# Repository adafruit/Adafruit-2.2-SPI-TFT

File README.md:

# Adafruit 2.2" 18-bit color TFT LCD display with microSD card breakout 

<a href="http://www.adafruit.com/products/1480"><br/>Click here to purchase one from the Adafruit shop</a>

These are the Eagle CAD files for the Adafruit 2.2" 18-bit color TFT LCD display with microSD card breakout:
  * https://www.adafruit.com/products/797 (older 220x178 HX8340BN version)
  * http://www.adafruit.com/products/1480 (newer 320x240 ILI9340 version)

This lovely little display breakout is the best way to add a small, colorful and bright display to any project. Since the display uses 3-wire SPI to communicate and has its own pixel-addressable frame buffer, it can be used with every kind of microcontroller. Even a very small one with low memory and few pins available! 

The 2.2" display has 220x176 color pixels. Unlike the low cost "Nokia 6110" and similar LCD displays, which are CSTN type and thus have poor color and slow refresh, this display is a true TFT! The TFT driver (HX8340) can display full 18-bit color (262,144 shades!). And the LCD will always come with the same driver chip so there's no worries that your code will not work from one to the other. 

The breakout has the TFT display soldered on (it uses a delicate flex-circuit connector) as well as a ultra-low-dropout 3.3V regulator and a 3/5V level shifter so you can use it with 3.3V or 5V power and logic. We also had a little space so we placed a microSD card holder so you can easily load full color bitmaps from a FAT16/FAT32 formatted microSD card.

## License

Adafruit invests time and resources providing this open source design, 
please support Adafruit and open-source hardware by purchasing 
products from Adafruit!

Designed by Limor Fried/Ladyada for Adafruit Industries.
Creative Commons Attribution/Share-Alike, all text above must be included in any redistribution
All text above must be included in any redistribution

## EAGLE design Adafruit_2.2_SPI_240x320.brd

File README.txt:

Adafruit 2.2" 18-bit color TFT LCD display with microSD card breakout

These are the Eagle CAD files for the Adafruit 2.2" 18-bit color TFT LCD display with microSD card breakout:
  ----> https://www.adafruit.com/products/797 (older 220x178 HX8340BN version)
  ----> http://www.adafruit.com/products/1480 (newer 320x240 ILI9340 version)

Adafruit invests time and resources providing this open source design, please support Adafruit and open-source hardware by purchasing products from Adafruit!

This lovely little display breakout is the best way to add a small, colorful and bright display to any project. Since the display uses 3-wire SPI to communicate and has its own pixel-addressable frame buffer, it can be used with every kind of microcontroller. Even a very small one with low memory and few pins available! 

The 2.2" display has 220x176 color pixels. Unlike the low cost "Nokia 6110" and similar LCD displays, which are CSTN type and thus have poor color and slow refresh, this display is a true TFT! The TFT driver (HX8340) can display full 18-bit color (262,144 shades!). And the LCD will always come with the same driver chip so there's no worries that your code will not work from one to the other. 

The breakout has the TFT display soldered on (it uses a delicate flex-circuit connector) as well as a ultra-low-dropout 3.3V regulator and a 3/5V level shifter so you can use it with 3.3V or 5V power and logic. We also had a little space so we placed a microSD card holder so you can easily load full color bitmaps from a FAT16/FAT32 formatted microSD card.

All text above must be included in any redistribution

Designed by Limor Fried/Ladyada for Adafruit Industries.
Creative Commons Attribution/Share-Alike, all text above must be included in any redistribution

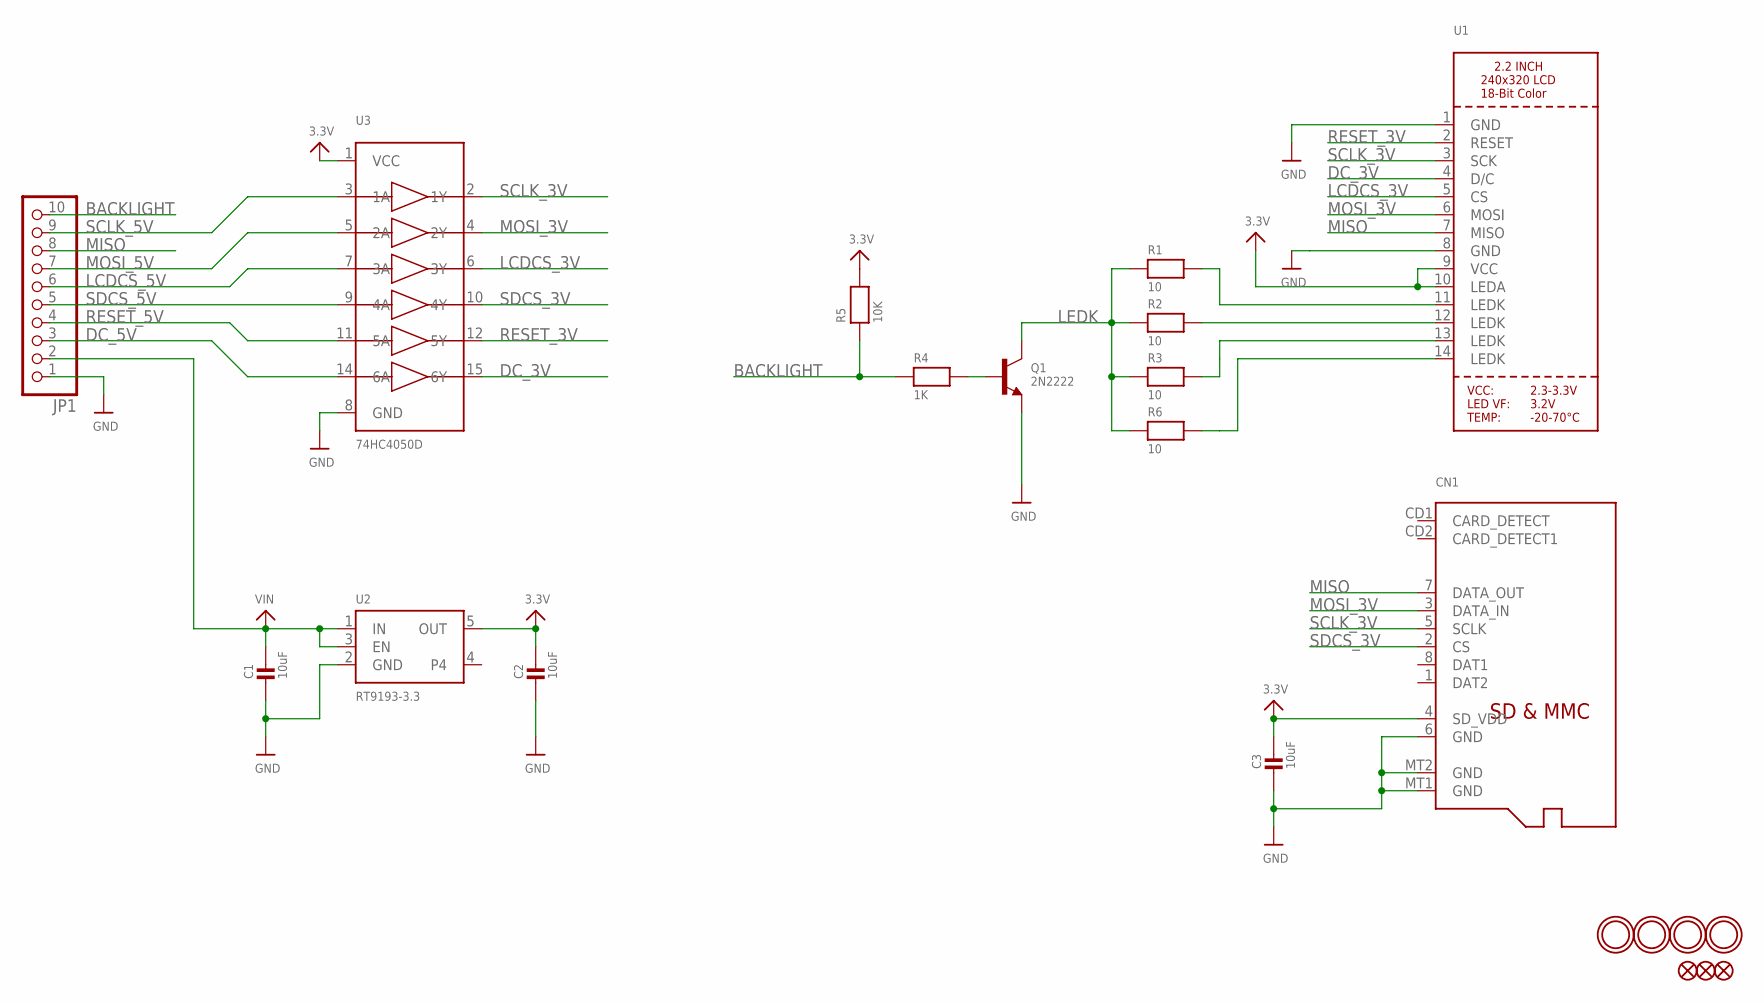
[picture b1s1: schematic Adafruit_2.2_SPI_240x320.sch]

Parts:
C1, C2, C3: 10uF; _0805MP
CN1: MICROSD
FID1, FID2, FID3: FIDUCIAL""; FIDUCIAL_1MM
JP1: HEADER-1X1070MIL; 1X10_ROUND70
Q1: 2N2222; SOT23-WIDE
R1, R2, R3, R6: 10; _0805MP
R4: 1K; _0805MP
R5: 10K; _0805MP
U1: DISP_LCD_TM022HDH26; TM022HDH26_2.2IN_LCD
U2: RT9193-3.3; SOT23-5
U3: 74HC4050D; SOIC16
U$2, U$3, U$4, U$5: MOUNTINGHOLE2.5; MOUNTINGHOLE_2.5_PLATED

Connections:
3.3V: C2.1, C3.1, CN1.4 (SD_VDD), R5.2, U1.9 (VCC), U1.10 (LEDA), U2.5 (OUT), U3.1 (VCC)
BACKLIGHT: JP1.10, R4.1, R5.1
DC_3V: U1.4 (D/C), U3.15 (6Y)
DC_5V: JP1.3, U3.14 (6A)
GND: C1.2, C2.2, C3.2, CN1.6 (GND), CN1.MT1 (GND), CN1.MT2 (GND), JP1.1, Q1.2 (E), U1.1 (GND), U1.8 (GND), U2.2 (GND), U3.8 (GND)
LCDCS_3V: U1.5 (CS), U3.6 (3Y)
LCDCS_5V: JP1.6, U3.7 (3A)
LEDK: Q1.3 (C), R1.1, R2.1, R3.1, R6.1
MISO: CN1.7 (DATA_OUT), JP1.8, U1.7 (MISO)
MOSI_3V: CN1.3 (DATA_IN), U1.6 (MOSI), U3.4 (2Y)
MOSI_5V: JP1.7, U3.5 (2A)
unnamed: R1.2, U1.11 (LEDK)
unnamed: R2.2, U1.12 (LEDK)
unnamed: R3.2, U1.13 (LEDK)
unnamed: Q1.1 (B), R4.2
unnamed: R6.2, U1.14 (LEDK)
RESET_3V: U1.2 (RESET), U3.12 (5Y)
RESET_5V: JP1.4, U3.11 (5A)
SCLK_3V: CN1.5 (SCLK), U1.3 (SCK), U3.2 (1Y)
SCLK_5V: JP1.9, U3.3 (1A)
SDCS_3V: CN1.2 (CS), U3.10 (4Y)
SDCS_5V: JP1.5, U3.9 (4A)
VIN: C1.1, JP1.2, U2.1 (IN), U2.3 (EN)

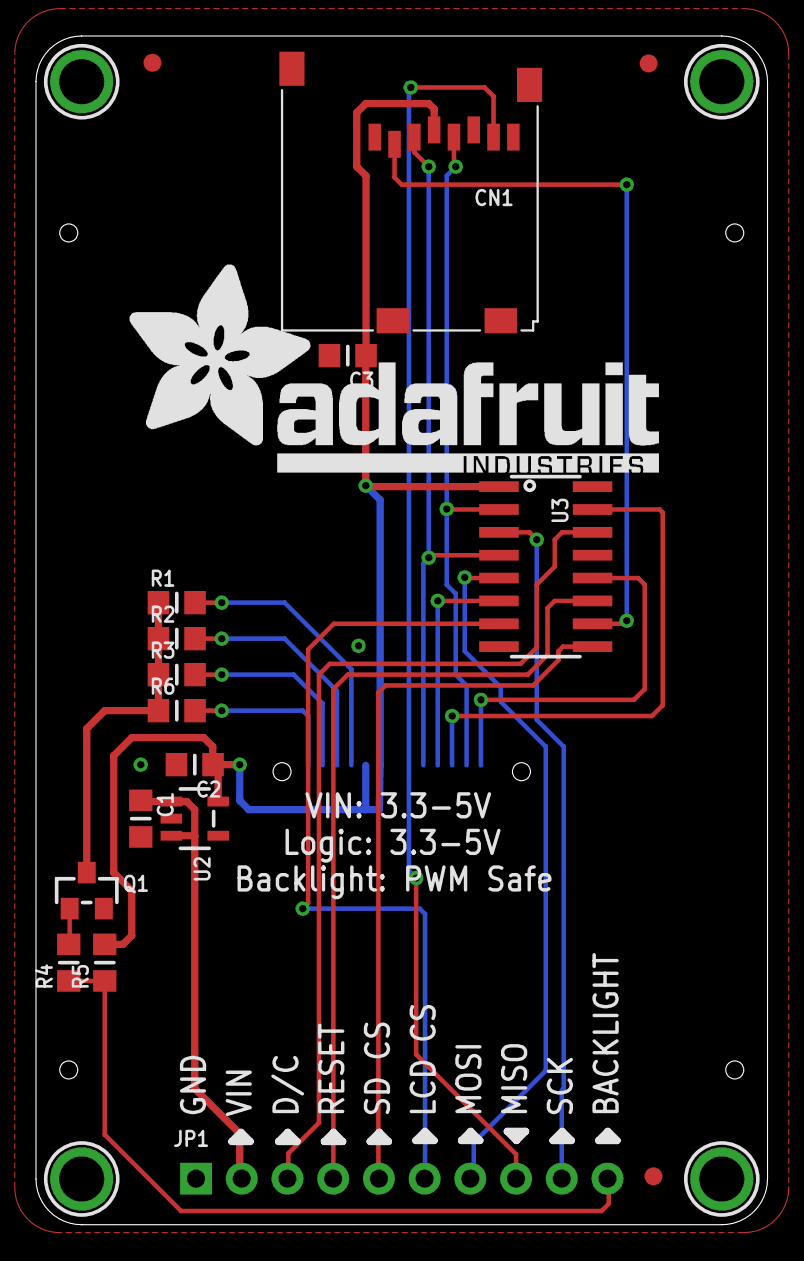
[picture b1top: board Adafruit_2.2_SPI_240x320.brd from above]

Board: 2 copper layers, 40.6 x 66.0 mm, 23 parts (1 on the bottom side), 23 nets.

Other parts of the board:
U$20: ADAFRUIT_TEXT_30MM

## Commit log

2012-05-04 Adafruit 2.2" 18-bit color TFT LCD display with microSD card breakout
    Adafruit 2.2" 18-bit color TFT LCD display with microSD card breakout
2014-03-14 Added the new ILI9340 version!
2014-03-14 updated readme for 2 version
2014-03-15 Added PNG of ILI9340 schematic
    PNG of ILI9340 schematic
2019-05-07 readme + image
